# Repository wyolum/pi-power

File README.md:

pi-power
========

Full featured power options for the Raspberry Pi.  12V, 5V, Lipo, with push/push on/off and power meter.

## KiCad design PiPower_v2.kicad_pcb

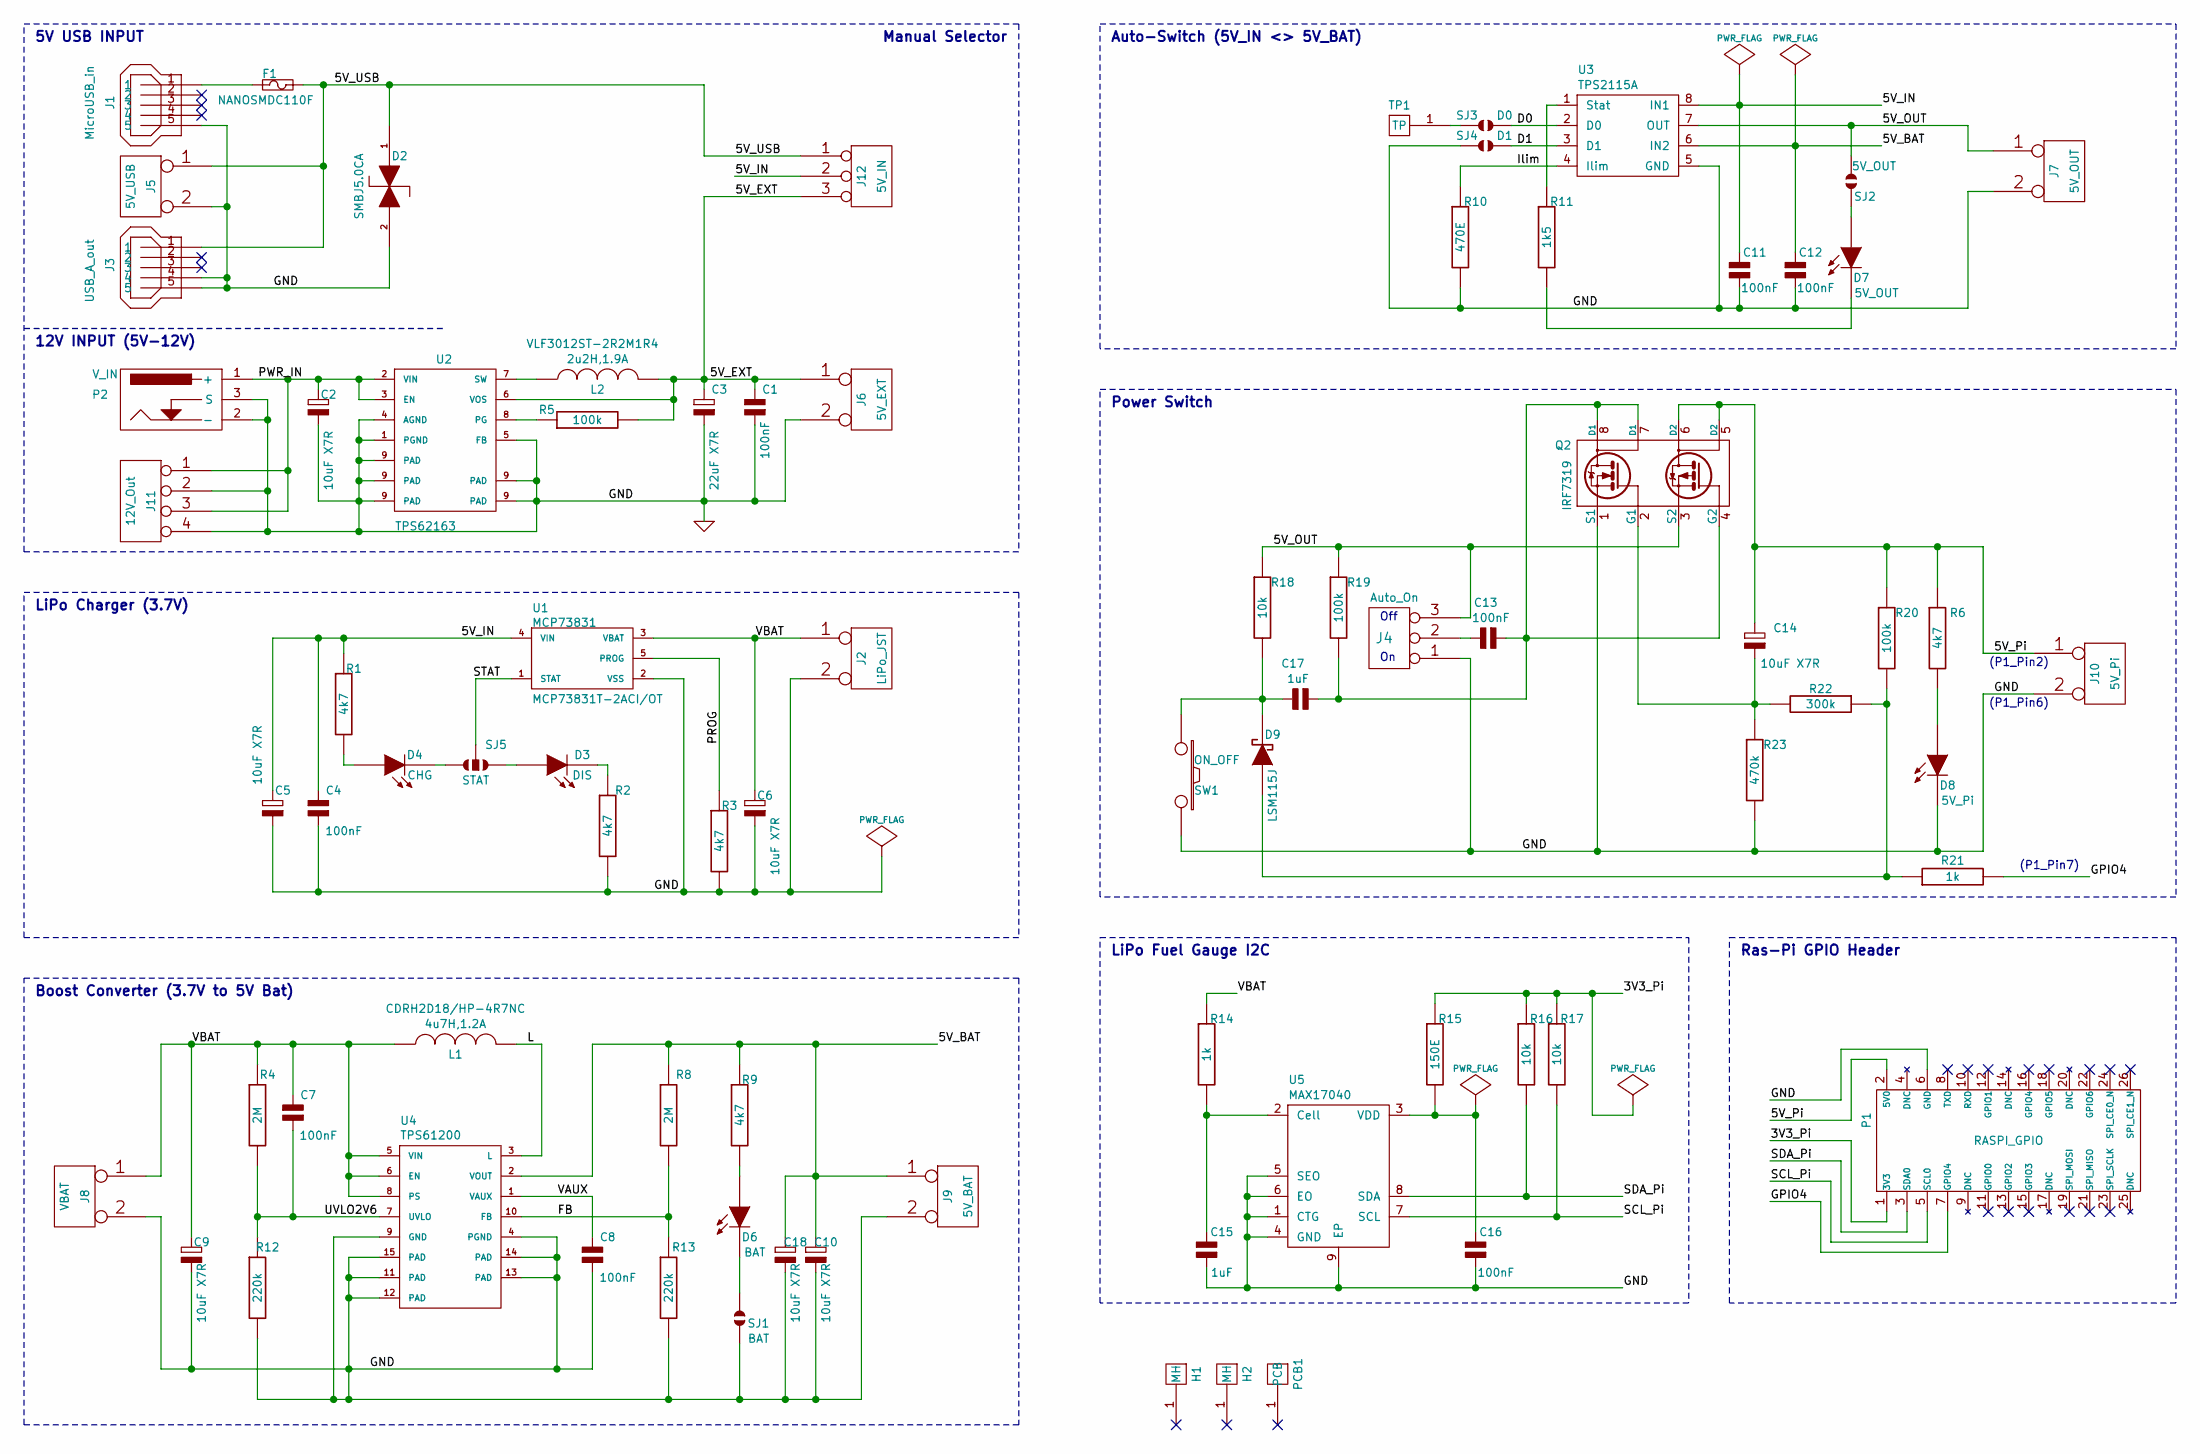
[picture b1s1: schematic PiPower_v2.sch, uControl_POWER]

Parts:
C1, C4, C7, C8, C11, C12, C13, C16: 100nF; c_0805
C2, C5, C6, C9, C10, C14, C18: 10uF X7R; C_ELCO_SMD
C3: 22uF X7R; c_0805
C15, C17: 1uF; c_0805
D2: SMBJ5.0CA; diode-DO214AA
D3: DIS; led_0805
D4: CHG; led_0805
D6: BAT; led_0805
D7: 5V_OUT; led_0805
D8: 5V_Pi; led_0805
D9: LSM115J; diode-DO214BA
F1: NANOSMDC110F; f_1206
H1, H2: MH; vite_3mm
J1: MicroUSB_in; USB_B_Micro
J2: LiPo_JST; CONN_JST-2_SMD
J3: USB_A_out; USB_A
J4: Auto_On; Header_3
J5: 5V_USB; Header_2
J6: 5V_EXT; Header_2
J7: 5V_OUT; Header_2
J8: VBAT; Header_2
J9: 5V_BAT; Header_2
J10: 5V_Pi; Header_2
J11: 12V_Out; Header2x2
J12: 5V_IN
L1: 4u7H,1.2A; Inductor_SMD1; Mfr_PN CDRH2D18/HP-4R7NC
L2: 2u2H,1.9A; Inductor_SMD1; Mfr_PN VLF3012ST-2R2M1R4
P1: RASPI_GPIO; Header_GPIO
P2: V_IN; JACK_ALIM
PCB1: PCB
Q2: IRF7319; SO8E
R1, R2, R3, R6, R9: 4k7; r_0805
R4, R8: 2M; r_0805
R5, R19, R20: 100k; r_0805
R10: 470E; r_0805
R11: 1k5; r_0805
R12, R13: 220k; r_0805
R14, R21: 1k; r_0805
R15: 150E; r_0805
R16, R17, R18: 10k; r_0805
R22: 300k; r_0805
R23: 470k; r_0805
SJ1: BAT; ShortLink
SJ2: 5V_OUT; ShortLink
SJ3: D0; ShortLink
SJ4: D1; ShortLink
SJ5: STAT
SW1: ON_OFF; SW_PB_V_H
TP1: TP; Breakout
U1: MCP73831
U2: TPS62163
U3: TPS2115A; TPS2115_SON
U4: TPS61200; TPS61200_QFN10
U5: MAX17040; MAX17040_TDFN

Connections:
/3V3_Pi: P1.1 (3V3), R15.1, R16.1, R17.1
/5V_BAT: C10.1, C12.2, C18.1, J9.1, R8.1, R9.1, U3.6 (IN2), U4.2 (VOUT)
/5V_EXT: C1.2, C3.1, J6.1, J12.3, L2.2, R5.2, U2.6 (VOS)
/5V_IN: C4.2, C5.1, C11.2, J12.2, R1.1, U1.4 (VIN), U3.8 (IN1)
/5V_OUT: J4.3, J7.1, Q2.3 (S2), R18.1, R19.1, SJ2.1, U3.7 (OUT)
/5V_Pi: C14.1, J10.1, P1.2 (5V0), Q2.5 (D2), Q2.6 (D2), R6.1, R20.1
/5V_USB: D2.1, F1.1, J3.1, J5.1, J12.1
/D0: SJ3.1, U3.2 (D0)
/D1: SJ4.1, U3.3 (D1)
/FB: R8.2, R13.1, U4.10 (FB)
/GPIO4: P1.7 (GPIO4), R21.2
/Ilim: R10.1, U3.4 (Ilim)
/L: L1.2, U4.3 (L)
/PROG: R3.1, U1.5 (PROG)
/PWR_IN: C2.1, J11.1, J11.3, P2.1 (+), U2.2 (VIN), U2.3 (EN)
/SCL_Pi: P1.5 (SCL0), R17.2, U5.7 (SCL)
/SDA_Pi: P1.3 (SDA0), R16.2, U5.8 (SDA)
/STAT: SJ5.2, U1.1 (STAT)
/UVLO2V6: C7.1, R4.2, R12.1, U4.7 (UVLO)
/VAUX: C8.2, U4.1 (VAUX)
/VBAT: C6.1, C7.2, C9.1, J2.1, J8.1, L1.1, R4.1, R14.1, U1.3 (VBAT), U4.5 (VIN), U4.6 (EN), U4.8 (PS)
unnamed: C15.2, R14.2, U5.2 (Cell)
unnamed: C16.2, R15.2, U5.3 (VDD)
unnamed: D6.1 (A), R9.2
unnamed: F1.2, J1.1
unnamed: D7.1 (A), SJ2.2
unnamed: D6.2 (K), SJ1.1
unnamed: L2.1, U2.7 (SW)
unnamed: R5.1, U2.8 (PG)
unnamed: D4.2 (K), SJ5.3
unnamed: D3.1 (A), SJ5.1
unnamed: D4.1 (A), R1.2
unnamed: D3.2 (K), R2.1
unnamed: C13.1, J4.2
unnamed: C17.1, D9.2 (K), R18.2, SW1.1
unnamed: C13.2, C17.2, Q2.4 (G2), Q2.7 (D1), Q2.8 (D1), R19.2
unnamed: C14.2, Q2.2 (G1), R22.2, R23.1
unnamed: D9.1 (A), R20.2, R21.1, R22.1
unnamed: D8.1 (A), R6.2
unnamed: R11.1, U3.1 (Stat)
unnamed: D7.2 (K), R11.2
unnamed: SJ3.2, TP1.1

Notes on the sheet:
(P1_Pin2)
(P1_Pin7)
Off
(P1_Pin6)
5V USB INPUT
12V INPUT (5V-12V)
Manual Selector
LiPo Charger (3.7V)
Boost Converter (3.7V to 5V Bat)
Auto-Switch (5V_IN <> 5V_BAT)
Power Switch
LiPo Fuel Gauge I2C
Ras-Pi GPIO Header

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
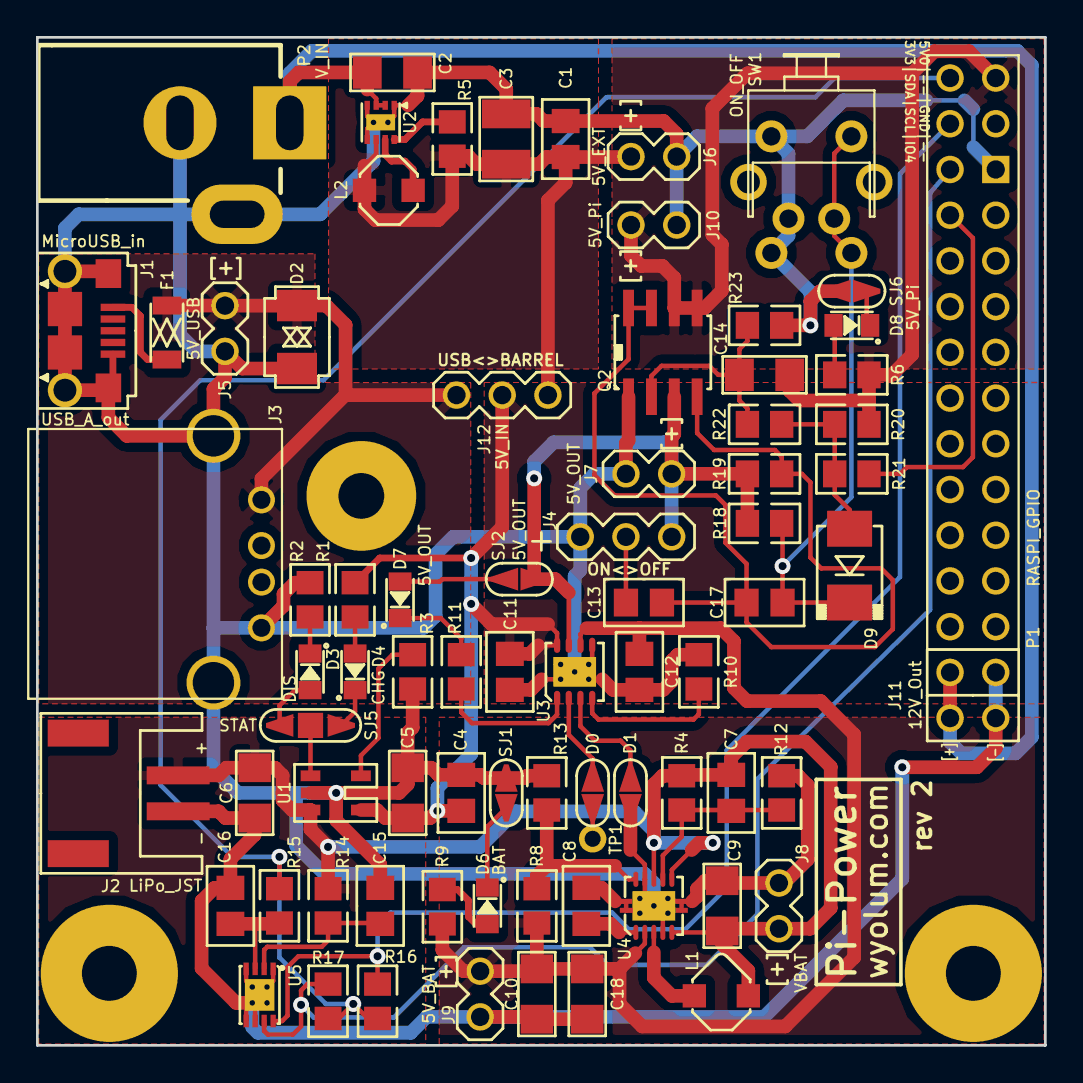
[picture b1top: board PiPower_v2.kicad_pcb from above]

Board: 2 copper layers, 56.0 x 56.0 mm, 81 parts (0 on the bottom side), 44 nets.

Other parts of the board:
SJ6: 5V_Pi; ShortLink

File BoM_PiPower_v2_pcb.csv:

"Id";"Designator";"Package";"Quantity";"Designation";"Supplier and ref";
1;"C1,C7,C8,C11,C12,C4,C13,C16";"c_0805";8;"100nF";;;
2;"L1";"Inductor_SMD1";1;"4u7H,1.2A";;;
3;"R1,R2,R9,R6";"r_0805";4;"2k2";;;
4;"R3";"r_0805";1;"2k";;;
5;"R4,R8";"r_0805";2;"2M";;;
6;"R5,R19,R20";"r_0805";3;"100k";;;
7;"R10";"r_0805";1;"470E";;;
8;"R11";"r_0805";1;"1k5";;;
9;"R12,R13";"r_0805";2;"220k";;;
10;"R14,R21";"r_0805";2;"1k";;;
11;"SJ1";"ShortLink";1;"BAT";;;
12;"SW1";"SW_PB_V_H";1;"ON_OFF";;;
13;"U1";"MCP73831";1;"MCP73831";;;
14;"C15,C17";"c_0805";2;"1uF";;;
15;"D2";"diode-DO214AA";1;"SMBJ5.0CA";;;
16;"D3";"led_0805";1;"DIS";;;
17;"D4";"led_0805";1;"CHG";;;
18;"D6";"led_0805";1;"BAT";;;
19;"D7";"led_0805";1;"5V_OUT";;;
20;"D9";"diode-DO214BA";1;"LSM115J";;;
21;"F1";"f_1206";1;"NANOSMDC110F";;;
22;"J2";"CONN_JST-2_SMD";1;"LiPo_JST";;;
23;"J4";"Header_3";1;"Auto_On";;;
24;"J6";"Header_2";1;"5V_EXT";;;
25;"J7";"Header_2";1;"5V_OUT";;;
26;"J8";"Header_2";1;"VBAT";;;
27;"J9";"Header_2";1;"5V_BAT";;;
28;"J10";"Header_2";1;"5V_Pi";;;
29;"P2";"JACK_ALIM";1;"V_IN";;;
30;"Q2";"SO8E";1;"IRF7319";;;
31;"R15";"r_0805";1;"150E";;;
32;"R16,R17,R18";"r_0805";3;"10k";;;
33;"R22";"r_0805";1;"300k";;;
34;"SJ3";"ShortLink";1;"D0";;;
35;"SJ4";"ShortLink";1;"D1";;;
36;"TP1";"Breakout";1;"TP";;;
37;"J1";"USB_B_Micro";1;"MicroUSB_in";;;
38;"U4";"TPS61200_QFN10";1;"TPS61200";;;
39;"J3";"USB_A";1;"USB_A_out";;;
40;"U3";"TPS2115_SON";1;"TPS2115A";;;
41;"U5";"MAX17040_TDFN";1;"MAX17040";;;
42;"H1,H2";"vite_3mm";2;"MH";;;
43;"J5";"Header_2";1;"5V_USB";;;
44;"PCB1";"PCB";1;"PCB";;;
45;"P1";"Header_GPIO_3";1;"RASPI_GPIO";;;
46;"C2,C5,C6,C9,C10,C14,C18";"c_1206";7;"10uF X7R";;;
47;"C3";"c_1210";1;"22uF X7R";;;
48;"D8";"led_0805";1;"5V_Pi";;;
49;"J12";"Header_3";1;"5V_IN";;;
50;"R23";"r_0805";1;"470k";;;
51;"SJ2";"ShortLink";1;"5V_OUT";;;
52;"SJ5";"ShortLink2";1;"STAT";;;
53;"L2";"Inductor_SMD2";1;"2u2H,1.9A";;;
54;"U2";"TPS62163_DSG";1;"TPS62163";;;
55;"J11";"Header2x2";1;"12V_Out";;;
56;"SJ6";"ShortLink";1;"5V_Pi";;;

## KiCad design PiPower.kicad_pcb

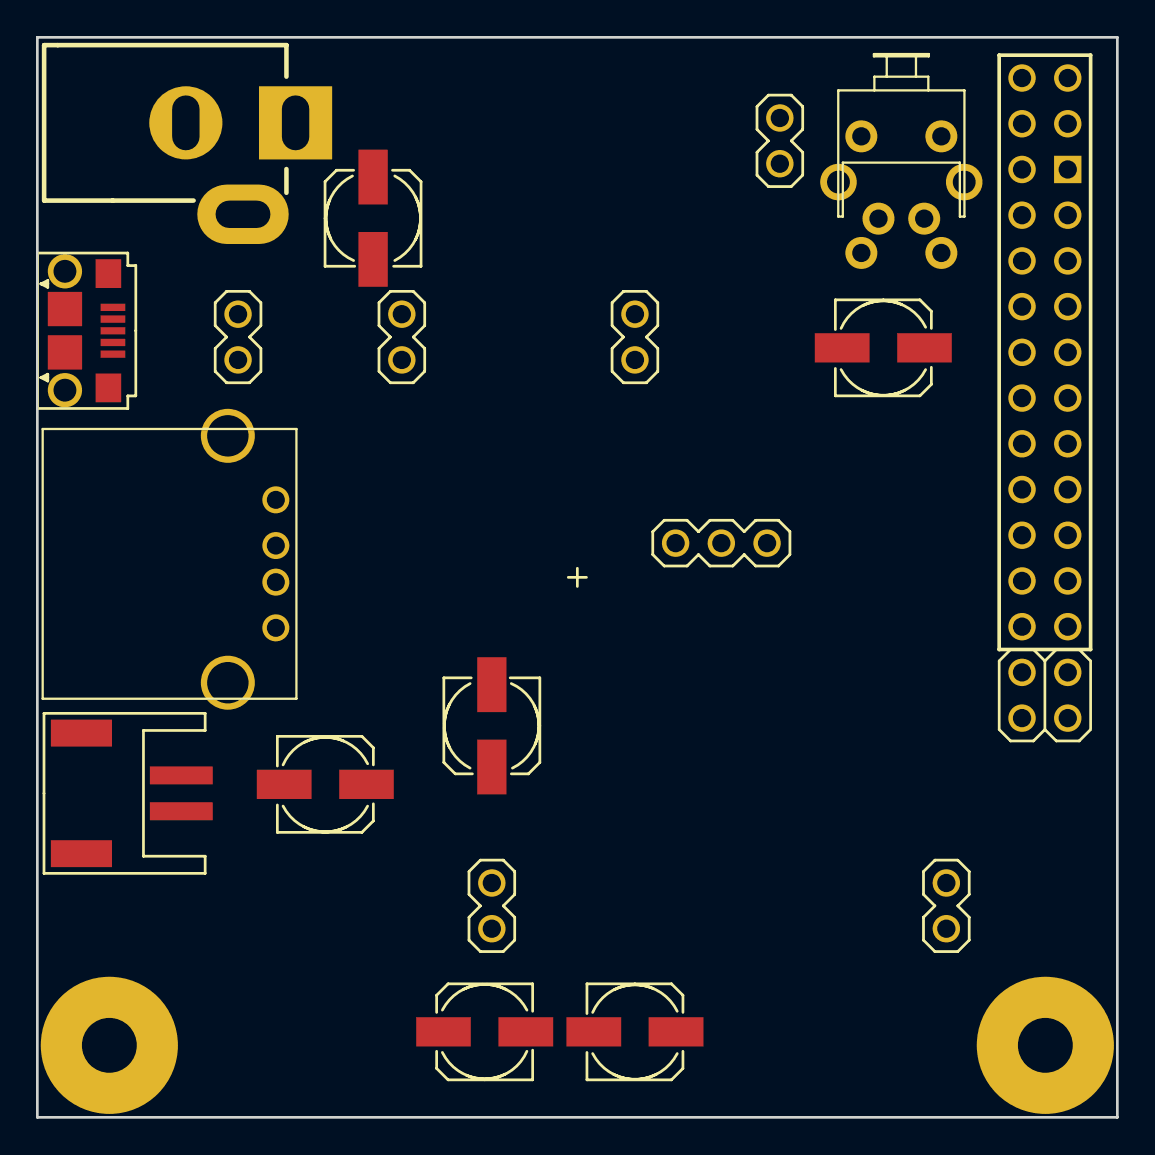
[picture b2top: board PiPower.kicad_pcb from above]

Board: 2 copper layers, 60.0 x 60.0 mm, 23 parts (0 on the bottom side), 7 nets, no tracks yet.

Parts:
C2: 100u,25V; C_ELCO_SMD
C5, C6: 10u; C_ELCO_SMD
C9, C14: 10uF; C_ELCO_SMD
C10: 22uF; C_ELCO_SMD
H1, H2: MH; vite_3mm
J1: MicroUSB_in; USB_B_Micro
J2: LiPo_JST; CONN_JST-2_SMD
J3: USB_A_out; USB_A
J4: Auto_On; Header_3
J5: 5V_USB; Header_2
J6: 5V_EXT; Header_2
J7: 5V_IN; Header_2
J8: VBAT; Header_2
J9: 5V_BAT; Header_2
J10: 5V_Pi; Header_2
J11: 12V_Out; Header2x2
P1: RASPI_GPIO; Header_GPIO
P2: V_IN; JACK_ALIM
PCB1: PCB
SW1: ON_OFF; SW_PB_V_H

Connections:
/5V_BAT: C10.1, J9.1
/5V_IN: C5.1, J4.3, J7.1
/5V_Pi: C14.1, J10.1, P1.2
/5V_USB: J3.1, J5.1
/PWR_IN: J11.1, P2.1
/VBAT: C6.1, C9.1, J2.1, J8.1
GND: C2.2, C5.2, C6.2, C9.2, C10.2, J1.5, J2.2, J3.4, J3.5, J4.1, J5.2, J6.2, J7.2, J8.2, J9.2, J10.2, J11.2, P1.6, P2.2, P2.3, SW1.2

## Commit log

2013-10-20 project folder clean up, file renaming etc
2013-10-21 folder cleanup, files renamed (PiPower_v2)and other initial changes
2013-10-21 1310211033 PiPower work in progress
2013-10-23 added power switch AP2401 data
2013-10-27 1310271049 PiPower work in progress
2013-11-02 1311021119 Schematic complete, needs to be verified
2013-11-03 1311031620 Schematic complete, needs to be verified
2013-11-04 1311050158 preliminary track layout complete
2013-11-05 1311051633 track layout complete
2013-11-05 1311051958 added some zones
2013-11-05 1311051125 added more zones
2013-11-06 1311060933 changed some resistor values for charging current and LEDs
2013-11-08 1311081530 changed board size to 56x56mm, Gerbers ready
2013-11-08 1311081535 changed board size to 56x56mm, Gerbers ready
2013-11-20 new BoM work in progress
2013-11-20 1311201004 BoM complete
2013-11-21 1311211133 Final v2 BoM and Gerber ZIP
